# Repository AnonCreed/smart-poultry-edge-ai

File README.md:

# Edge-AI Based Predictive Closed Control System for Smart Poultry Farming

**Minor Project** -- Department of Electronics and Computer Engineering,
Thapathali Campus, Institute of Engineering (IOE), Tribhuvan University.
Submitted in partial fulfillment of the Bachelor's degree in Electronics,
Communication and Information Engineering (August 2026), under the
supervision of **Er. Anup Shrestha**, by Amir Bhattarai, Aviral Adhikari,
Balram Sharma Kandel, and Bikash BK.

## About

Poultry farming is a major part of Nepal's agricultural sector, and most
farms still run open-house systems where the indoor environment tracks
whatever the weather outside is doing. During the brooding stage (the first
two weeks after hatching) chicks are especially sensitive to temperature
swings, humidity, and ammonia buildup from droppings -- conditions farmers
today mostly manage by manual observation and experience, which means
unfavorable changes can go unnoticed until they've already hurt the flock.

This project came out of discussions around the bird-flu outbreaks in Nepal
in 2026. Actually detecting or preventing disease was out of scope for a
minor project, but keeping a poultry house's environment inside a safe band
is a problem we could tackle directly: continuous IoT sensing, an on-device
ML model that forecasts where temperature and ammonia are heading (not just
where they are), and automated fan/heater control that reacts before a
threshold is crossed rather than after.

That's what this repository is: the full system, not just the dashboard --

- **`hardware/esp32/`** -- an ESP32 sensor node reading temperature, humidity
  and ammonia (DHT11 + MQ-137), driving the fan/heater relays.
- **`hardware/esp32s3_master/`** -- an ESP32-S3 master node that receives
  those readings over ESP-NOW and runs an on-device TFLite Micro model to
  forecast the next reading and flag an ammonia-spike probability, before
  handing everything to the backend.
- **`hardware/kicad/`** -- the KiCad schematic and PCB for the sensor node.
- **`telemetry/`** -- the Django backend: ingestion API, server-side rule
  classifier, and the live dashboard (charts, actuator control, console
  feed, historical export).
- **`docs/`** -- the written report and the proposal/final defense decks
  submitted for the degree.

See [Documentation & Reports](#documentation--reports) for the full report
and defense decks, and [Designs](#designs) for the PCB.

## System at a glance

Django backend, Edge-AI-ready JSON REST API, server-side environmental
classifier, a two-board ESP-NOW hardware pipeline (ESP32 sensor node +
ESP32-S3 master node running an on-device TFLite Micro forecast/spike
model), a standalone sensor simulator for development without hardware, and
a standard Bootstrap 5 dashboard (dual-line forecast charts, actuator
control, live console feed, historical reports/CSV export; Bootstrap and
Chart.js are both vendored locally for air-gapped operation).

## Architecture

```
sensor_simulator.py  ──HTTP POST──>  /api/telemetry/submit/
   (Virtual sensor,                     │ validate -> classify -> persist
    5 s cadence,                        ▼
    random walk +               PoultryTelemetry (SQLite, indexed timestamp)
    anomaly injection)                  │
                                        ▼
dashboard (browser)  ──HTTP GET──>  /api/telemetry/historical/?hours=N
   (5 s polling loop feeds metrics grid, charts, audit log)
```

Physical hardware replaces the simulator with a two-board pipeline (the
Django/dashboard side above is unchanged either way):

```
hardware/esp32/ (DevKit V1, sensor node)  --ESP-NOW-->  hardware/esp32s3_master/ (ESP32-S3, master node)
   DHT11 + MQ-137 + fan/heater                     TFLite Micro forecast + spike model
              ^                                              |
              `------------ ESP-NOW (classification) <-------'  --WiFi/HTTP--> /api/telemetry/submit/
```

The master node is the only board that talks to Django; the sensor node only
ever exchanges fixed-size binary structs with the master over ESP-NOW. See
`hardware/esp32/README.md` and `hardware/esp32s3_master/README.md` for the full pipeline,
wiring, and the MAC-address pairing procedure the two boards need before
they can talk to each other.

| Component | Path |
|---|---|
| Data model + classification enum | `telemetry/models.py` |
| Pure classifier decision framework + spike-risk threshold | `telemetry/classifier.py` |
| API views (submit / historical) + dashboard shell | `telemetry/views.py` |
| URL map | `telemetry/urls.py`, `config/urls.py` |
| Virtual sensor client (dev/demo, no hardware needed) | `sensor_simulator.py` |
| ESP32 sensor-node firmware (DHT11 + MQ-137, ESP-NOW, actuator loop) | `hardware/esp32/src/main.cpp`, `hardware/esp32/include/config.h` |
| ESP32-S3 master-node firmware (ESP-NOW receive, TFLite Micro inference, WiFi/HTTP to Django) | `hardware/esp32s3_master/src/main.cpp`, `hardware/esp32s3_master/include/config.h` |
| Dashboard template | `telemetry/templates/telemetry/dashboard.html` |
| Console stylesheet / client runtime | `telemetry/static/telemetry/dashboard.css`, `dashboard.js` |
| Unit tests (classifier + API + forecast + spike-risk contracts) | `telemetry/tests.py` |

## Classifier rules (first match wins)

1. `ammonia_level > 15.0` -> `CRITICAL_AMMONIA` (dark red background, white text)
2. `temperature > 35.0` (live reading OR the Edge-AI forecast alone) -> `HEAT_STRESS_WARNING` (orange border, orange text) -- no humidity condition
3. `temperature < 18.0` -> `LOW_TEMP_ALERT` (deep blue text, light blue accents)
4. otherwise -> `OPTIMAL_ENVIRONMENT` (charcoal grid, solid green indicator dot)

Classification is computed server-side at ingestion, before the INSERT, so every
stored row is complete and immutable. Thresholds are exposed in the historical
API response so the front end never hardcodes them.

## API

`POST /api/telemetry/submit/`
```json
{
  "temperature": 29.4,
  "humidity": 61.2,
  "ammonia_level": 8.7,
  "predicted_temperature": null,
  "predicted_ammonia": null,
  "predicted_spike_probability": null
}
```
Returns `201` with the persisted record including `predicted_class`.

Forecast channels (`predicted_temperature`, `predicted_ammonia`,
`predicted_spike_probability`) are optional and nullable: absent key, explicit
null, and numeric value are all accepted, since the ESP32-S3 master node may not
be linked yet. When numeric, `predicted_temperature`/`predicted_ammonia` are
bounds-checked against the same physical envelope as their live counterparts,
and `predicted_spike_probability` (the master's TFLite Micro spike-classifier
output) is bounds-checked to `[0, 1]`. All three serialize back as JSON null
when absent, so chart clients can rely on key presence. Classification is
always driven by live readings only; forecasts and spike risk are advisory
overlays. Payloads with missing live fields, non-numeric values, or readings
outside physical/probability envelopes are rejected with `400`.

`GET /api/telemetry/historical/?hours=24`
Returns records in the trailing window, ascending chronologically, plus the active
threshold set — ready for direct ingestion by chart libraries.

## Running the system

Two terminals.

Terminal 1 — backend and dashboard:
```bash
pip install -r requirements.txt
python manage.py migrate
python manage.py runserver 0.0.0.0:8000
# Dashboard (this machine):  http://127.0.0.1:8000/
# Dashboard (other devices, e.g. a phone on the same WiFi): http://<this-machine's-LAN-IP>:8000/
```

Binding `0.0.0.0` (not the default `127.0.0.1`) matters if you're using the
physical ESP32-S3 master node -- it needs to reach this over WiFi, and it
finds the LAN IP itself via UDP broadcast discovery (see
`hardware/esp32s3_master/README.md`), so there's no IP to hardcode on either
side. `ALLOWED_HOSTS` is left open (`"*"`) in `config/settings.py` for the
same reason -- this is a dev-only server, never expose it beyond a trusted
LAN.

Terminal 2 — virtual sensor:
```bash
python sensor_simulator.py
# Edge-AI forecast emulation is ON by default so the KPI forecast lines,
# dashed chart series, console (Pred: ...) markers, and the AI spike-risk
# card all have live numbers. To transmit null forecasts/spike-risk
# (matching the deployment state before the ESP32-S3 master node is linked):
python sensor_simulator.py --no-edge-ai
```

The simulator transmits every 5 seconds using an Ornstein-Uhlenbeck-style random
walk (Gaussian step + mean reversion) per channel, and superimposes two anomaly
generators: a triangular thermal spike exceeding 37 C every 2 minutes, and an
ammonia accumulation ramp that climbs past 30 PPM until a simulated ventilation
fan engages and extracts it back to baseline.

## Tests

```bash
python manage.py test telemetry
```

Covers classifier rule precedence (ammonia dominance, heat-stress from live
reading or forecast alone, low-temperature boundary), ingestion validation,
nullable forecast-channel contracts (absent key, explicit null, populated,
invalid type), and historical ordering/threshold contracts.

## Hardware firmware (two boards: ESP32 sensor node + ESP32-S3 master node)

Two firmware projects ship the physical pipeline; both must be flashed and
paired (by MAC address) for the hardware to work end-to-end.

- **`hardware/esp32/`** -- ESP32 DevKit V1 sensor node. Reads DHT11 on GPIO4 and
  MQ-137 on GPIO34 every 5 s, and sends the readings over **ESP-NOW** to the
  master node (no HTTP, no JSON on this board). Drives an ON/OFF fan relay
  (GPIO32) and an ON/OFF heater relay (GPIO25) from the classification the
  master relays back. See `hardware/esp32/README.md` for the pin map and
  MQ-137 calibration
  procedure.
- **`hardware/esp32s3_master/`** -- ESP32-S3 master node. Receives sensor readings
  over ESP-NOW, runs an on-device TFLite Micro model to forecast the next
  temperature/ammonia reading and an ammonia-spike probability, then POSTs
  the combined record to Django using the same JSON contract the Python
  simulator uses. Relays Django's classification back to the sensor node
  over ESP-NOW. See `hardware/esp32s3_master/README.md` for the model details, the
  Arduino IDE flashing steps, and the MAC-pairing procedure required before
  either board can talk to the other.

Quickstart (flash the master first -- you need its printed MAC address to
configure the sensor node):
```bash
cd hardware/esp32s3_master
# Arduino IDE: install libraries per README.md, edit config_master.h
# (WIFI_SSID, WIFI_PASSWORD, API_BASE_URL, SENSOR_NODE_MAC_ADDR),
# then upload esp32s3_master.ino and note the printed "Receiver MAC".

cd ../esp32
# Edit include/config.h: WIFI_SSID, WIFI_PASSWORD (same network as the
# master), MASTER_MAC_ADDR (from the step above).
pio run                 # Compile
pio run -t upload       # Flash over USB
pio device monitor      # Serial diagnostics at 115200 baud
# Copy this board's printed MAC back into hardware/esp32s3_master/config_master.h's
# SENSOR_NODE_MAC_ADDR and reflash the master.
```

The virtual simulator and the physical firmware pipeline are contract-
compatible: both ultimately POST the same JSON payload shape to Django, so
the backend and dashboard cannot tell them apart. The Python simulator
remains useful for CI, demos, and development without hardware in the loop.

## Views

Two tab-switched views share a single polling loop, so the console tail
accumulates in the background even while the user is on the Overview.

### Overview Dashboard
- KPI cards: instantaneous readings with desaturated state accents (colored
  value text plus a 2px left-border highlight; backgrounds stay untouched).
  Each forecastable channel shows a muted secondary line beneath the primary
  value: `AI Forecast: 27.8 degC`, `AI Forecast: 8.4 ppm`. When the ESP32-S3
  master node's link is inactive the line reads `AI Forecast: pending`.
- **AI spike risk** card: the ESP32-S3 master node's TFLite Micro spike-
  classifier probability, rendered as a percentage. Escalates
  ok -> warn -> crit as the probability crosses the calibrated threshold
  (echoed from the API, never hardcoded twice) and twice that threshold.
  Reads `Master node: pending` until the master node is linked.
- Dual-line charts (full vertical breathing room): solid stroke for live
  sensor data, dashed light stroke for Edge-AI forecasts (`spanGaps: false`,
  so null forecast points render as gaps and a fully-null channel is simply
  invisible while remaining mounted), plus a dashed threshold baseline.

### System Logs Feed
Dedicated full-page console. Append-only tail keyed by record id; each new
ingestion appends one line in the format
`[YYYY-MM-DD HH:MM:SS] INGESTION SUCCESS -> T: 27.4C (Pred: 27.8C) | RH: 60.2% | NH3: 8.1ppm (Pred: 8.4ppm) | STATE: OPTIMAL | SPIKE_RISK: 14%`
with text tinted by classification. When a forecast channel is null the
inline marker reads `(Pred: n/a)`; the `SPIKE_RISK` segment is omitted
entirely (not `n/a`) when the master node hasn't reported a probability yet.
Includes a rolling 200-line buffer and a pause-scroll control. The server
emits the same line via the `telemetry.ingest` logger, so `journalctl` and
the browser can be cross-referenced without translation.

## Designs

KiCad schematic + PCB for the ESP32 sensor node live in `hardware/kicad/`
(`kicad.kicad_pro`, `.kicad_sch`, `.kicad_pcb`, `.kicad_prl` -- open the
`.kicad_pro` in KiCad 9). It lays out the ESP32 DevKit V1 footprint alongside
the DHT11, MQ-137, fan/heater relay drive, and terminal-block wiring
described in `hardware/esp32/README.md`.

## Documentation & Reports

| Document | Path |
|---|---|
| Minor project report (full, 81 pages) | [`docs/minor_project_report.pdf`](docs/minor_project_report.pdf) |
| Proposal presentation | [`docs/presentations/proposal_presentation.pdf`](docs/presentations/proposal_presentation.pdf) |
| Final defense presentation | [`docs/presentations/final_presentation.pdf`](docs/presentations/final_presentation.pdf) |
| Hardware & firmware architecture deep-dive | [`HARDWARE_DOCUMENTATION.md`](HARDWARE_DOCUMENTATION.md) |

## Team

| Name | Roll No. |
|---|---|
| Amir Bhattarai | THA080BEI005 |
| Aviral Adhikari | THA080BEI011 |
| Balram Sharma Kandel | THA080BEI012 |
| Bikash BK | THA080BEI015 |

Supervised by **Er. Anup Shrestha**, Department of Electronics and Computer
Engineering, Thapathali Campus, Institute of Engineering, Tribhuvan University.

## License

MIT -- see [`LICENSE`](LICENSE).

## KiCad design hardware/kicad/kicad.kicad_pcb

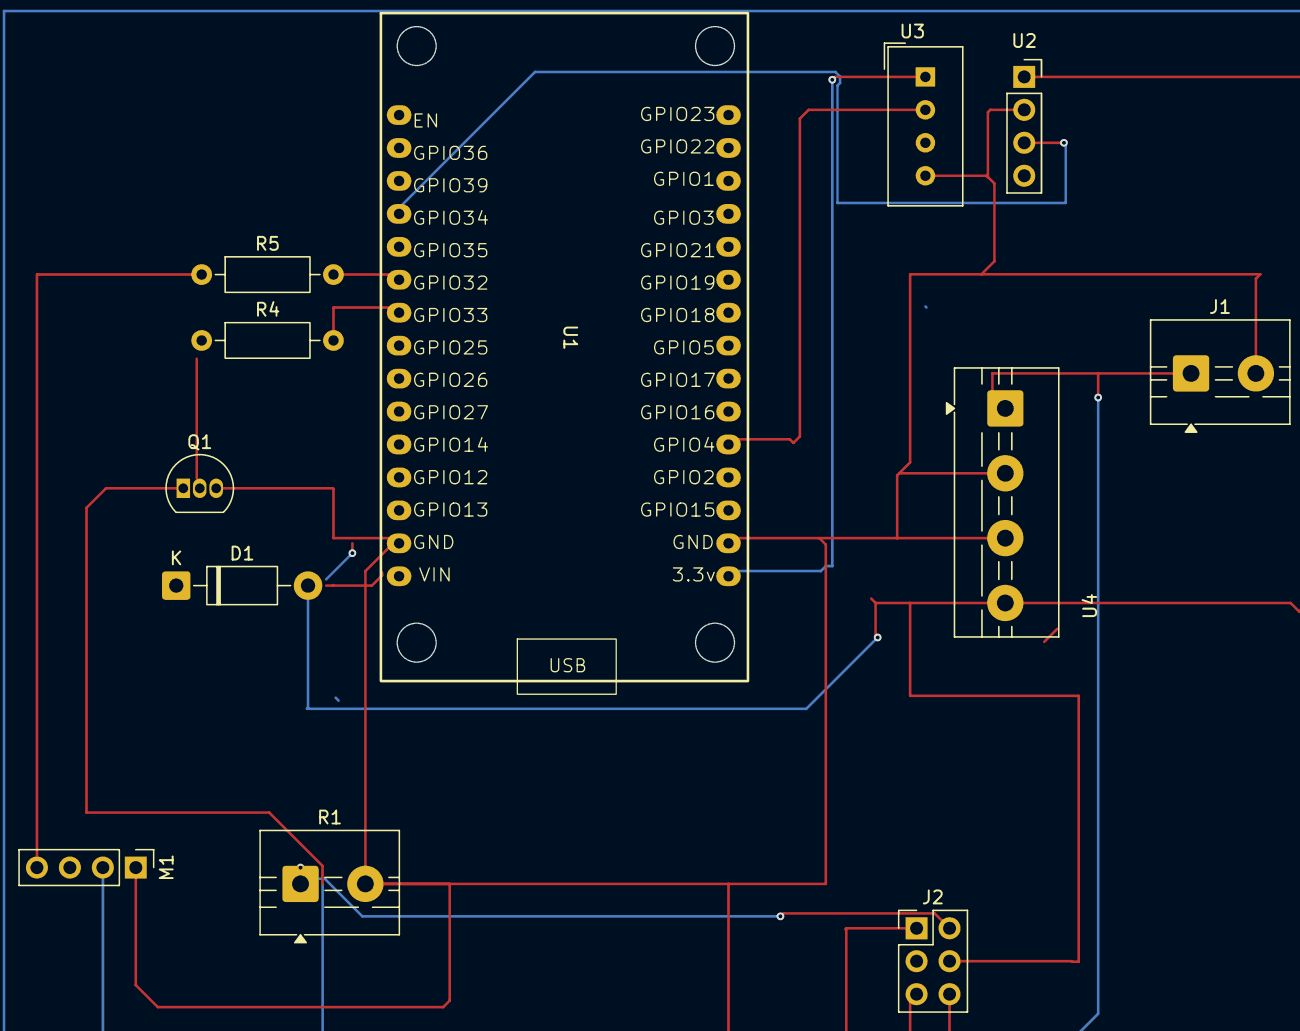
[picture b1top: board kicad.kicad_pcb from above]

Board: 2 copper layers, 12 parts (0 on the bottom side), 13 nets.

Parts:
D1: 1N4007; D_DO-41_SOD81_P10.16mm_Horizontal
J1: 12V-input; TerminalBlock_MaiXu_MX126-5.0-02P_1x02_P5.00mm
J2: Conn_01x03_Pin; PinHeader_2x03_P2.54mm_Vertical
M1: Fan_4pin; PinHeader_1x04_P2.54mm_Vertical
Q1: BC547; TO-92_Inline
R1: Heater; TerminalBlock_MaiXu_MX126-5.0-02P_1x02_P5.00mm
R4: 1K; R_Axial_DIN0207_L6.3mm_D2.5mm_P10.16mm_Horizontal
R5: 200; R_Axial_DIN0207_L6.3mm_D2.5mm_P10.16mm_Horizontal
U1: ESP32_30pin
U2: MQ-137; PinSocket_1x04_P2.54mm_Vertical
U3: DHT22; Aosong_DHT11_5.5x12.0_P2.54mm
U4: DCDC_StepDown_LM2596; TerminalBlock_MaiXu_MX126-5.0-04P_1x04_P5.00mm

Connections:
+3.3V: U1.16 (3.3v), U3.1 (VCC)
+5V: D1.2 (A), J2.4 (VCC), U2.1 (VCC), U4.4 (Vout)
+12V: J1.1, J2.1 (COM), M1.2 (+), U4.1 (Vin)
/DHT_DATA: U1.20 (GPIO4), U3.2 (DATA)
/MQ_DATA: U1.12 (GPIO34), U2.3 (A0)
/PWM_FAN: M1.4 (PWM), R5.1
/PWM_HEATER: Q1.2 (B), R4.1
GND: J1.2, J2.5 (GND), M1.1 (-), Q1.3 (E), R1.2, U1.2 (GND), U1.17 (GND), U2.2 (GND), U3.4 (GND), U4.2 (GND), U4.3 (GND)
unnamed: D1.1 (K), U1.1 (VIN)
unnamed: J2.6 (IN), Q1.1 (C)
unnamed: J2.2 (NO), R1.1
unnamed: R4.2, U1.8 (GPIO25)
unnamed: R5.2, U1.10 (GPIO32)

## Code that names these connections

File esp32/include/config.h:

// ============================================================================
// config.h -- Compile-time configuration for the ESP32 edge node.
//
// All hardware-specific magic numbers live here. Pin assignments mirror the
// KiCad schematic (2x15 pin socket, ESP32 DevKit V1); do not change without
// updating the board layout and this comment block simultaneously.
// ============================================================================
#pragma once

// ---------------------------------------------------------------------------
// Network
// ---------------------------------------------------------------------------
// WiFi credentials are loaded from credentials.h (gitignored).
// Copy esp32/include/credentials.h.example -> credentials.h and fill in
// your SSID and password before building.
//
// This node no longer talks to Django directly (see HARDWARE_DOCUMENTATION.md
// "ESP-NOW pipeline"): it joins the WiFi AP only so it (a) lands on the same
// 2.4 GHz channel as the ESP32-S3 master, which ESP-NOW requires, and (b) can
// pull real wall-clock time via NTP for the model's hour/month cyclic
// features. Telemetry itself goes out over ESP-NOW to MASTER_MAC_ADDR below;
// the master owns the WiFi/HTTP leg to Django.
#include "credentials.h"

// MAC address of the ESP32-S3 master node's WiFi station interface. Flash
// esp32s3_master/ first and copy the "Receiver MAC: XX:XX:XX:XX:XX:XX" line
// it prints on boot into this array (byte order matches, no reversal needed).
// Placeholder until the master's actual boot-log MAC is read back.
#define MASTER_MAC_ADDR { 0xFF, 0xFF, 0xFF, 0xFF, 0xFF, 0xFF }

// NTP time source for the model's hour-of-day / month-of-year cyclic
// features (see esp32s3_master/esp32s3_inference_receiver.ino).
// GMT_OFFSET_SEC = 20700 = Nepal Standard Time (UTC+5:45).
#define NTP_SERVER            "pool.ntp.org"
#define GMT_OFFSET_SEC         20700
#define DAYLIGHT_OFFSET_SEC    0
#define NTP_SYNC_TIMEOUT_MS    5000

// ---------------------------------------------------------------------------
// Timing
// ---------------------------------------------------------------------------
// Transmit cadence must match the dashboard's polling interval (5 s) so the
// chart tail advances one point per refresh -- no aliasing or empty ticks.
#define SAMPLE_INTERVAL_MS 5000

// WiFi reconnect back-off: linear, capped. Wall-clock reconnection latency
// stays below one sample interval even at the ceiling.
#define WIFI_RETRY_MS      2000
#define WIFI_MAX_RETRIES   10

// ---------------------------------------------------------------------------
// Pin map (mirrors schematic; do not divorce)
// ---------------------------------------------------------------------------
// DHT22 data line. GPIO4 is a general-purpose IO with hardware pull-up
// support -- the standard 10 kOhm pull-up between DATA and 3V3 is assumed
// on the sensor breakout.
#define PIN_DHT_DATA    4

// MQ-137 analog output. GPIO34 is INPUT-ONLY on the classic ESP32 and is
// wired to ADC1 channel 6 -- ADC1 is the only ADC block usable while WiFi
// is active, so this channel selection is mandatory, not incidental.
// Sensor output must be scaled to 0-3.3 V by an external divider before
// reaching this pin; MQ modules that swing to 5 V will damage the SoC.
#define PIN_MQ_DATA     34

// PWM outputs. Series 200 Ohm gate resistors (R5, R4) are on the board.
// LEDC channels 0/1 drive these; frequency and resolution below.
#define PIN_PWM_FAN     32
#define PIN_PWM_HEATER  33

// LEDC (ESP32 PWM peripheral) parameters. 25 kHz is above audible range so
// four-pin PC fans do not whine; 8-bit gives 0-255 duty granularity which
// is finer than the actuator needs.
#define PWM_FAN_CHANNEL     0
#define PWM_HEATER_CHANNEL  1
#define PWM_FREQ_HZ         25000
#define PWM_RESOLUTION_BITS 8
#define PWM_DUTY_OFF        0
#define PWM_DUTY_ON         220   // ~86% -- headroom to protect MOSFET

// ---------------------------------------------------------------------------
// MQ-137 characteristic-curve calibration
// ---------------------------------------------------------------------------
// Rs computation uses the sensor's load resistor:
//   Rs = RL * (Vc - Vout) / Vout
// Then, from the datasheet's NH3 curve fit (log-log linearization):
//   PPM = MQ137_A * (Rs / R0) ^ MQ137_B
//
// R0 MUST be re-calibrated per unit in known-clean air after a ~24-48 hour
// burn-in. The value below is the datasheet nominal for illustration only.
// Recommended field procedure: expose sensor to ambient outdoor air, average
// Rs over 5 minutes, and store that value as R0 in NVS.
#define MQ137_VC_VOLTS   5.0f    // Sensor supply voltage
#define MQ137_RL_KOHMS   47.0f   // Load resistor on the module
#define MQ137_R0_KOHMS   3.6f    // Clean-air Rs baseline (CALIBRATE PER UNIT)
#define MQ137_A          102.2f
#define MQ137_B          -2.473f

// ADC oversampling. Averaging 16 raw samples suppresses the ESP32 ADC's
// well-known non-linearity noise floor by ~4x without introducing lag.
#define MQ_ADC_SAMPLES   16

// ADC full-scale: 12-bit resolution, 11 dB attenuation -> 0..3.3 V.
#define ADC_MAX_COUNTS   4095.0f
#define ADC_MAX_VOLTS    3.3f
